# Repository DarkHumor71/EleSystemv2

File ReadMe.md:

# EleSystemv2 - Smart Elevator & Building Management System

A comprehensive IoT-based elevator and building management system that integrates hardware control, electricity expense tracking, and a web-based admin dashboard. The system combines ESP32 microcontrollers for elevator control and QR code authentication with a full-stack web application for building and apartment management.

## 🏗️ Project Overview

EleSystemv2 is a multi-component system designed to modernize building management by:

- **Automated Elevator Control**: ESP32-based elevator controller with floor selection and queue management
- **QR Code Authentication**: Camera module for secure apartment access verification
- **Electricity Monitoring**: Track and calculate power consumption per apartment
- **Web Dashboard**: Modern React admin interface for managing buildings, apartments, and expenses
- **Role-Based Access**: Support for admin, moderator, and resident user roles

## 📁 Project Structure

```
EleSystemv2/
├── backend/              # Node.js/Express REST API
│   ├── config/          # Database and configuration files
│   ├── middleware/      # Authentication and authorization middleware
│   ├── models/          # MongoDB/Mongoose data models
│   └── routes/          # API route handlers
├── client/              # React admin dashboard
│   ├── public/          # Static assets
│   └── src/
│       ├── actions/     # Redux actions
│       ├── components/  # Reusable React components
│       ├── scenes/      # Page-level components
│       ├── reducers/    # Redux reducers
│       └── utils/       # Helper utilities
├── board/               # ESP32 elevator controller firmware
├── camera/              # ESP32-CAM QR code reader firmware
└── CAD/                 # KiCad PCB design files
```

## 🚀 Features

### Backend (REST API)

- **Authentication & Authorization**: JWT-based auth with role-based access control
- **Building Management**: CRUD operations for buildings with soft-delete support
- **Apartment Management**: Manage apartments within buildings, assign moderators
- **Expense Tracking**: Record and retrieve electricity usage data per apartment
- **Session Management**: Secure session handling for active users

### Frontend (React Dashboard)

- **Modern UI**: Material-UI components with light/dark mode
- **Data Visualization**: Charts and graphs for expense tracking
- **Building Administration**: Create and manage multiple buildings
- **Apartment Management**: Register apartments, generate QR codes
- **Expense Reports**: View and analyze electricity consumption
- **User Profiles**: Manage user information and roles

### Hardware Components

- **Elevator Controller** (`board/`):

  - 4-floor elevator control system
  - Button inputs and IR sensors per floor
  - Motor control (up/down)
  - 7-segment display for floor indication
  - Power monitoring and expense calculation
  - WiFi connectivity for data transmission

- **QR Code Reader** (`camera/`):
  - ESP32-CAM based authentication
  - Real-time QR code scanning
  - Server validation for apartment access
  - Scan cooldown to prevent duplicates

## 🛠️ Technology Stack

### Backend

- **Runtime**: Node.js
- **Framework**: Express.js
- **Database**: MongoDB with Mongoose ODM
- **Authentication**: JWT (jsonwebtoken)
- **Validation**: express-validator
- **Password Hashing**: bcryptjs

### Frontend

- **Framework**: React 18.3.1
- **State Management**: Redux Toolkit
- **UI Library**: Material-UI (MUI)
- **Routing**: React Router v7
- **Data Grid**: MUI X Data Grid
- **Charts**: Nivo, Chart.js
- **Form Handling**: Formik

### Hardware

- **Microcontroller**: ESP32 / ESP32-CAM
- **Connectivity**: WiFi (HTTP/HTTPS)
- **Development**: Arduino IDE
- **Libraries**: ESP32QRCodeReader, ArduinoJson, HTTPClient

### PCB Design

- **Tool**: KiCad
- **Modules**: Brain, Cabin, Display, Motor, Sensors

## 📋 Prerequisites

- **Node.js** v14+ and npm
- **MongoDB** v4+ (local or cloud instance)
- **Arduino IDE** with ESP32 board support
- **Git** for version control

## ⚙️ Installation & Setup

### 1. Clone the Repository

```bash
git clone https://github.com/DarkHumor71/EleSystemv2.git
cd EleSystemv2
```

### 2. Backend Setup

```bash
cd backend
npm install
```

Create a `config/default.json` file:

```json
{
  "mongoURI": "mongodb://localhost:27017/elesystem",
  "jwtSecret": "your_jwt_secret_key_here"
}
```

Or create a `.env` file with:

```
MONGO_URI=mongodb://localhost:27017/elesystem
JWT_SECRET=your_jwt_secret_key_here
PORT=5000
```

Start the backend server:

```bash
npm run server    # Development mode with nodemon
npm start         # Production mode
```

### 3. Frontend Setup

```bash
cd client
npm install
```

Update the proxy in `client/package.json` to match your backend URL:

```json
"proxy": "http://localhost:5000/"
```

Start the React development server:

```bash
npm start
```

### 4. Full Stack Development

From the `backend` directory:

```bash
npm run dev    # Runs both backend and frontend concurrently
```

### 5. Hardware Setup

#### Elevator Controller

1. Open `board/board.ino` in Arduino IDE
2. Update WiFi credentials:
   ```cpp
   const char* ssid = "your_wifi_ssid";
   const char* password = "your_wifi_password";
   ```
3. Update the server URL to match your backend IP
4. Upload to ESP32 board

#### Camera Module

1. Open `camera/camera.ino` in Arduino IDE
2. Update WiFi credentials and validation server URL
3. Upload to ESP32-CAM board

## 🔌 API Endpoints

### Authentication

- `POST /api/auth/login` - User login
- `POST /api/auth/apartment` - Apartment authentication

### Buildings

- `GET /api/building/:id` - Get building details
- `POST /api/building` - Create new building
- `PUT /api/building/:id` - Update building
- `DELETE /api/building/:id` - Soft delete building

### Apartments

- `GET /api/apartment/:id` - Get apartment details
- `POST /api/apartment` - Create new apartment
- `PUT /api/apartment/:id` - Update apartment
- `GET /api/apartment/exists` - Validate apartment (for QR authentication)

### Expenses

- `POST /api/expense` - Record electricity usage
- `GET /api/expense/apartment/:id` - Get expenses for apartment
- `GET /api/expense/building/:id` - Get all expenses for building
- `DELETE /api/expense/:id` - Delete expense record

## 🔐 Authentication & Authorization

The system uses JWT tokens with three permission levels:

1. **Admin**: Full system access, manage all buildings and apartments
2. **Moderator**: Building-specific access, manage apartments in their building
3. **Resident**: View personal apartment information and expenses

Middleware components:

- `auth.js` - Validates JWT token
- `admin.js` - Requires admin permissions
- `moderator.js` - Requires moderator permissions
- `building.js` - Validates building-level access
- `sameBuildingMod.js` - Ensures moderator belongs to the target building

## 📊 Data Models

### Building

- Name, email, address, city, state
- Soft delete support
- One-to-many relationship with apartments

### Apartment

- 4-digit PIN for authentication
- Apartment number (unique within building)
- Resident information (first name, last name, email)
- Moderator designation flag
- Reference to parent building

### Expense

- Time duration (in seconds)
- Power consumption (kWh)
- Cost calculation
- Timestamp of recording
- Reference to apartment

### Session

- Active user sessions
- Token management
- Automatic cleanup on server restart

## 🖥️ Dashboard Features

- **Admin Dashboard**: Overview of all buildings, apartments, and expenses
- **Moderator Dashboard**: Building-specific management
- **Apartment Dashboard**: Resident view of their expenses
- **Building List**: Browse and manage buildings
- **Apartment Management**: Add, edit, view apartments
- **Expense Tracking**: Visualize electricity usage over time
- **QR Code Generation**: Create QR codes for apartment authentication
- **Profile Management**: Update user information

## 🔧 Hardware Configuration

### Elevator Controller Pins

- **Buttons**: GPIO 19, 21, 22, 23 (floors 0-3)
- **IR Sensors**: GPIO 18, 5, 17, 16 (floors 0-3)
- **Motor Up**: GPIO 13
- **Motor Down**: GPIO 12
- **7-Segment Display**: Latch (26), Clock (25), Data (27)
- **Power Monitoring**: GPIO 34 (analog sensor)

### Camera Module

- ESP32-CAM with CAMERA_MODEL_AI_THINKER
- QR code scanning with 5-second cooldown
- HTTP validation with backend server

### FreeRTOS controller firmware

`board/board.ino` targets the ESP32 Arduino core, which includes FreeRTOS.
The elevator task runs every 10 ms at priority 4 and owns the buttons, floor
sensors, display, motor outputs, and emergency stop. A priority 1 network task
handles Wi-Fi, session verification, and expense uploads. An event group gates
motor operation on a verified session; a one-item FreeRTOS queue transfers an
expense report after the stop input is pressed. Upload failures are retried
without blocking motor shutdown. A full report queue latches a fault and
prevents another run.

The revised schematic uses an INA228 current monitor on I²C (SDA GPIO 16,
SCL GPIO 17). A third FreeRTOS task reads it and sends current samples through
a one-item queue; the motor task stays responsive if I²C is slow. Install the
`Adafruit INA228` Arduino library and its dependencies before building.
Set `SHUNT_RESISTANCE_OHMS` and `MAX_CURRENT_A` in `board/board.ino` to
match the assembled shunt and motor. The current values are provisional, so
expense measurements need calibration on hardware. The controller will not
enable its ready output until the INA228 initializes. The camera sketch
already uses a FreeRTOS QR scanning task.

## 🎨 Frontend Theming

The dashboard supports light and dark modes with customizable Material-UI themes. Theme configuration is in `client/src/theme.js`.

## 🧪 Testing

```bash
# Backend tests
cd backend
npm test

# Frontend tests
cd client
npm test
```

## 📦 Building for Production

### Frontend

```bash
cd client
npm run build
```

This creates an optimized production build in the `client/build` directory.

### Backend

The backend runs in production mode with:

```bash
cd backend
npm start
```

## 🤝 Contributing

Contributions are welcome! Please follow these steps:

1. Fork the repository
2. Create a feature branch (`git checkout -b feature/AmazingFeature`)
3. Commit your changes (`git commit -m 'Add some AmazingFeature'`)
4. Push to the branch (`git push origin feature/AmazingFeature`)
5. Open a Pull Request

## 📝 License

This project is licensed under the MIT License - see the [LICENSE](LICENSE) file for details.

## 👤 Author

**Mohammad Youssef** (DarkHumor71) **Ahmad Ayoub** (AhmadAybb) 

## 📞 Support

For questions, issues, or feature requests, please open an issue on the GitHub repository.

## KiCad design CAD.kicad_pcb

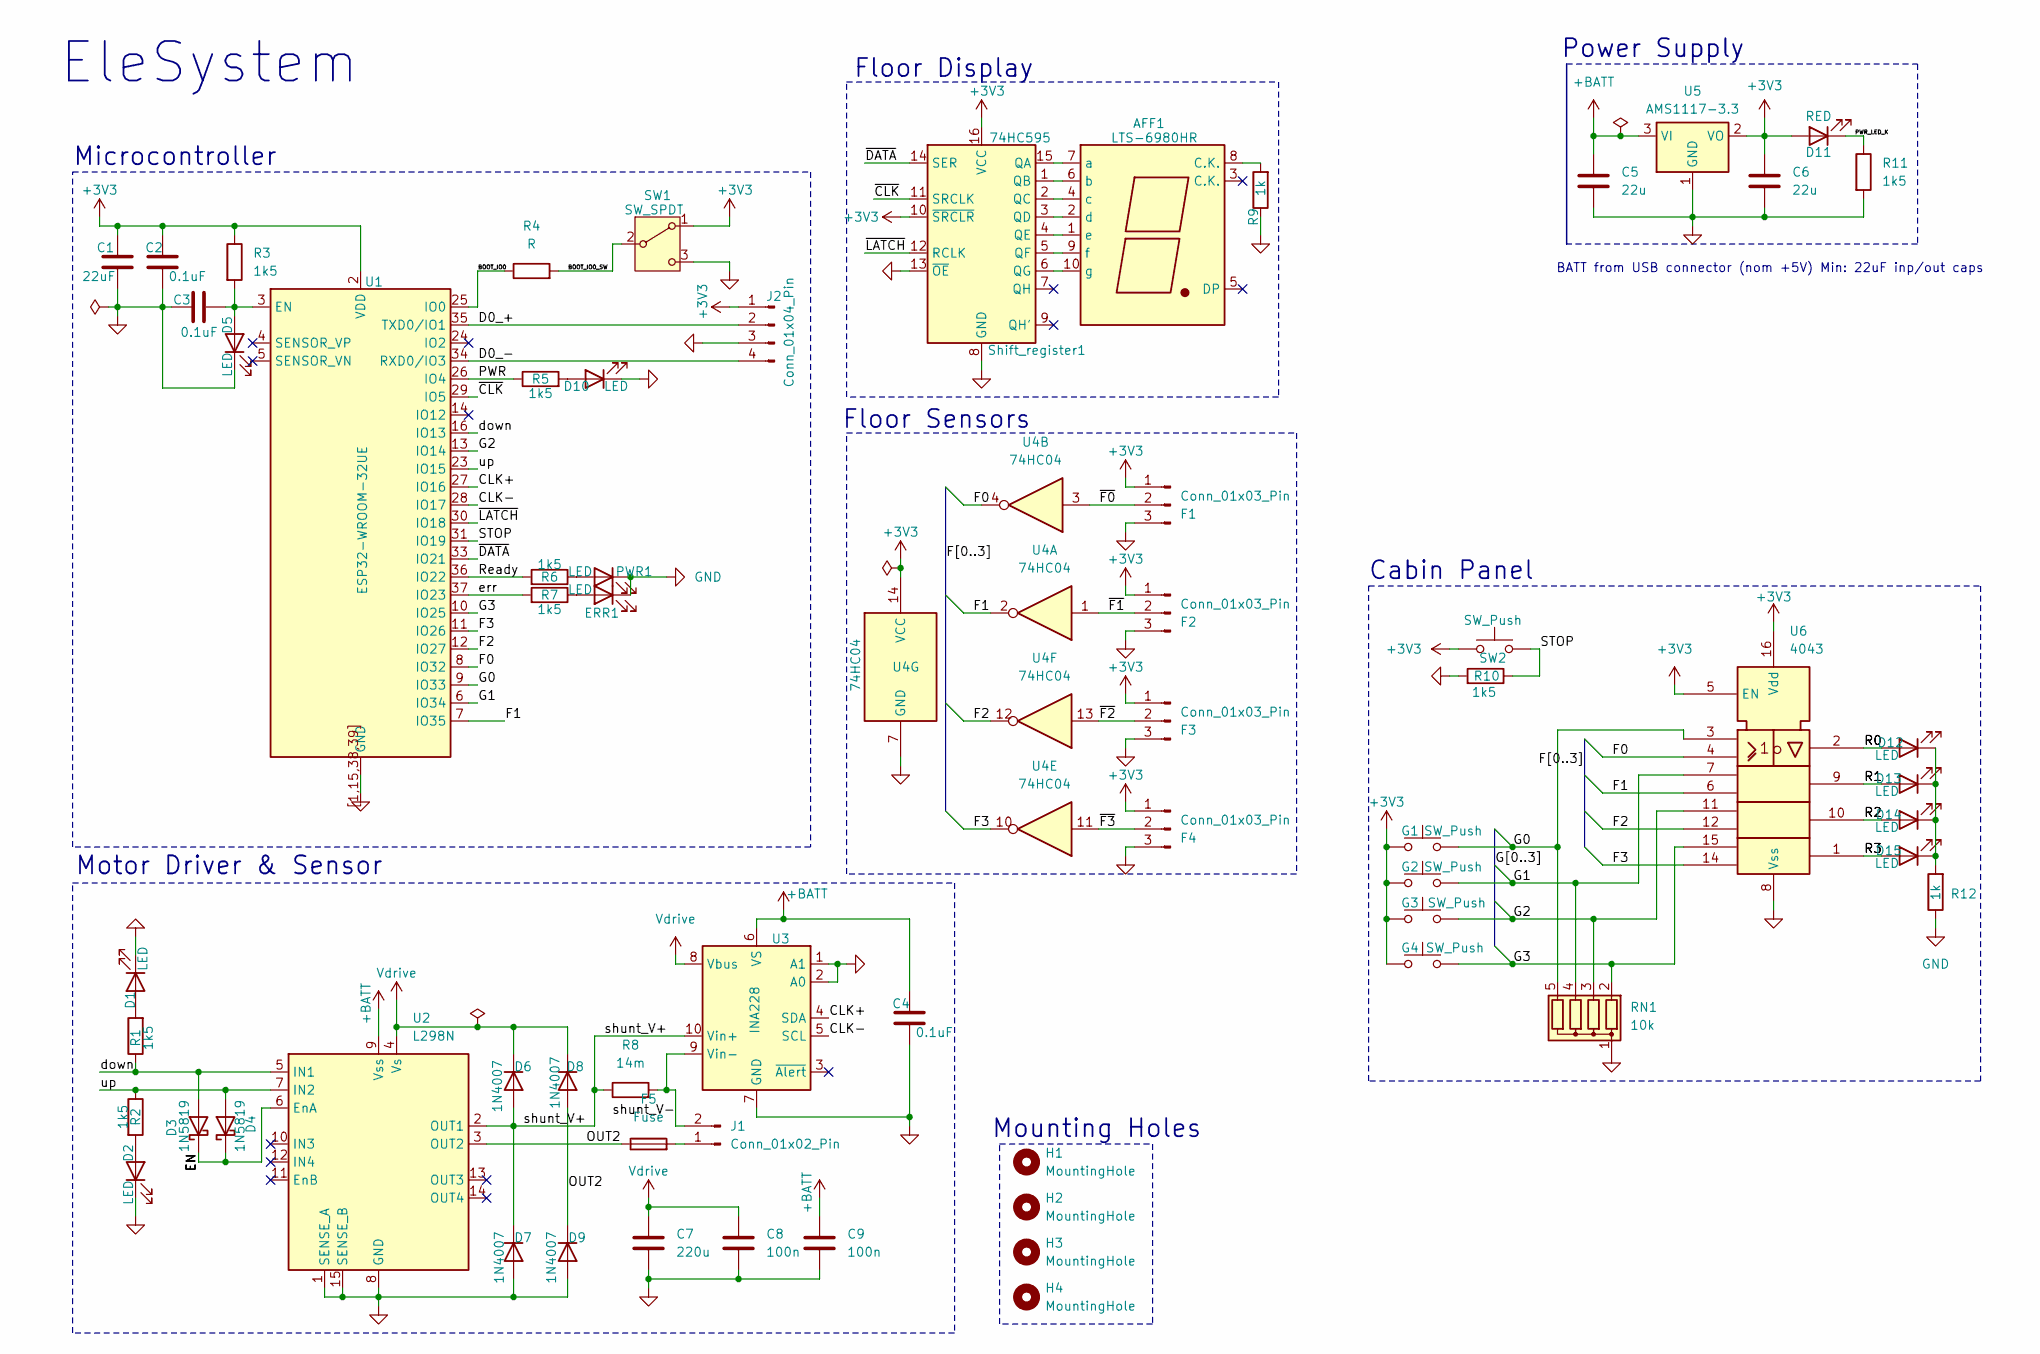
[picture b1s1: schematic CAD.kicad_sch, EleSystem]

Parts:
AFF1: LTS-6980HR; 7SegmentLED_LTS6760_LTS6780
C1: 22uF; C_0805_2012Metric
C2, C3, C4: 0.1uF; C_0402_1005Metric
C5, C6: 22u; C_0805_2012Metric
C7: 220u; C_Elec_8x10.2
C8, C9: 100n; C_0805_2012Metric
D1, D2, D5, D10: LED; LED_0603_1608Metric
D3, D4: 1N5819; D_1206_3216Metric
D6, D7, D8, D9: 1N4007; D_1206_3216Metric
D11: RED; LED_0603_1608Metric
D12, D13, D14, D15: LED; LED_1812_4532Metric_Pad1.30x3.40mm_HandSolder
ERR1: LED; LED_0603_1608Metric
F1, F2, F3, F4: Conn_01x03_Pin; PinHeader_1x03_P1.00mm_Vertical_SMD_Pin1Right
F5: Fuse; Fuse_0603_1608Metric
G1, G2, G3, G4: SW_Push; SW_PUSH_6mm_H7.3mm
H1, H2, H3, H4: MountingHole; MountingHole_2.2mm_M2
J1: Conn_01x02_Pin; PinHeader_1x02_P2.54mm_Vertical_SMD_Pin1Left
J2: Conn_01x04_Pin; PinHeader_1x04_P1.27mm_Vertical_SMD_Pin1Right
PWR1: LED; LED_0603_1608Metric
R1, R2, R3, R5, R6, R7, R10, R11: 1k5; R_0603_1608Metric
R4: R; R_0603_1608Metric
R8: 14m; R_2512_6332Metric
R9, R12: 1k; R_0603_1608Metric
RN1: 10k; R_Array_SIP5
SW1: SW_SPDT; SW_Slide_SPDT_Straight_CK_OS102011MS2Q
SW2: SW_Push; SW_Push_1P1T_NO_CK_KSC9xxG
Shift_register1: 74HC595; JEITA_SOIC-16_3.9x9.9mm_P1.27mm
U1: ESP32-WROOM-32UE
U2: L298N; TO-220-15_P2.54x5.08mm_StaggerOdd_Lead4.58mm_Vertical
U3: INA228; SMDIP-10_W7.62mm
U4: 74HC04; SSOP-16_4.4x5.2mm_P0.65mm
U5: AMS1117-3.3; SOT-223-3_TabPin2
U6: 4043; DIP-16_W7.62mm

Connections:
+3V3: C1.1, C2.1, C6.1, D11.2 (A), F1.1, F2.1, F3.1, F4.1, G1.1, G2.1, G3.1, G4.1, J2.1, R3.1, SW1.1 (A), SW2.2, Shift_register1.10 (~SRCLR), Shift_register1.16 (VCC), U1.2 (VDD), U4.14 (VCC), U5.2 (VO), U6.5 (EN), U6.16 (Vdd)
+BATT: C4.1, C5.1, C9.1, U2.9 (Vss), U3.6 (VS), U5.3 (VI); also elsewhere on the board
/BOOT_IO0: R4.1, U1.25 (IO0)
/BOOT_IO0_SW: R4.2, SW1.2 (B)
/CLK+: U1.27 (IO16), U3.4 (SDA)
/CLK-: U1.28 (IO17), U3.5 (SCL)
/D0_+: J2.2, U1.35 (TXD0/IO1)
/D0_-: J2.4, U1.34 (RXD0/IO3)
/EN: D3.1 (K), D4.1 (K), U2.6 (EnA)
/F0: U1.8 (IO32), U4.4, U6.4
/F1: U1.7 (IO35), U4.2, U6.6
/F2: U1.12 (IO27), U4.12, U6.12
/F3: U1.11 (IO26), U4.10, U6.14
/G0: G1.2, RN1.5 (R4), U1.9 (IO33), U6.3
/G1: G2.2, RN1.4 (R3), U1.6 (IO34), U6.7
/G2: G3.2, RN1.3 (R2), U1.13 (IO14), U6.11
/G3: G4.2, RN1.2 (R1), U1.10 (IO25), U6.15
/OUT2: D8.2 (A), D9.1 (K), F5.1, U2.3 (OUT2)
/PWR: R5.1, U1.26 (IO4)
/PWR_LED_K: D11.1 (K), R11.1
/R0: D12.2 (A), U6.2
/R1: D13.2 (A), U6.9
/R2: D14.2 (A), U6.10
/R3: D15.2 (A), U6.1
/Ready: R6.2, U1.36 (IO22)
/STOP: R10.1, SW2.1, U1.31 (IO19)
/down: D3.2 (A), R1.1, U1.16 (IO13), U2.5 (IN1)
/err: R7.2, U1.37 (IO23)
/shunt_V+: D6.2 (A), D7.1 (K), R8.1, U2.2 (OUT1), U3.10 (Vin+)
/shunt_V-: J1.2, R8.2, U3.9 (Vin-)
/up: D4.2 (A), R2.1, U1.23 (IO15), U2.7 (IN2)
/~CLK: Shift_register1.11 (SRCLK), U1.29 (IO5)
/~DATA: Shift_register1.14 (SER), U1.33 (IO21)
/~F0: F1.2, U4.3
/~F1: F2.2, U4.1
/~F2: F3.2, U4.13
/~F3: F4.2, U4.11
/~LATCH: Shift_register1.12 (RCLK), U1.30 (IO18)
GND: C1.2, C2.2, C3.1, C4.2, C5.2, C6.2, C7.2, C8.2, C9.2, D1.1 (K), D2.1 (K), D5.1 (K), D7.2 (A), D9.2 (A), D10.1 (K), ERR1.1 (K), F1.3, F2.3, F3.3, F4.3, J2.3, PWR1.1 (K), R9.1, R10.2, R11.2, R12.1, RN1.1 (common), SW1.3 (C), Shift_register1.8 (GND), Shift_register1.13 (~OE), U1.1 (GND), U1.15 (GND), U1.38 (GND), U1.39 (GND), U1.[1,15,38,39] (GND), U2.1 (SENSE_A), U2.8 (GND), U2.15 (SENSE_B), U3.1 (A1), U3.2 (A0), U3.7 (GND), U4.7 (GND), U5.1 (GND), U6.8 (Vss); also elsewhere on the board
unnamed: AFF1.8 (C.K.), R9.2
unnamed: AFF1.7 (a), Shift_register1.15 (QA)
unnamed: AFF1.6 (b), Shift_register1.1 (QB)
unnamed: AFF1.4 (c), Shift_register1.2 (QC)
unnamed: AFF1.2 (d), Shift_register1.3 (QD)
unnamed: AFF1.1 (e), Shift_register1.4 (QE)
unnamed: AFF1.9 (f), Shift_register1.5 (QF)
unnamed: AFF1.10 (g), Shift_register1.6 (QG)
unnamed: D1.2 (A), R1.2
unnamed: D2.2 (A), R2.2
unnamed: C3.2, D5.2 (A), R3.2, U1.3 (EN)
unnamed: D10.2 (A), R5.2
unnamed: D12.1 (K), D13.1 (K), D14.1 (K), D15.1 (K), R12.2
unnamed: ERR1.2 (A), R7.1
unnamed: F5.2, J1.1
unnamed: PWR1.2 (A), R6.1
Vdrive: C7.1, C8.1, D6.1 (K), D8.1 (K), U2.4 (Vs), U3.8 (Vbus)

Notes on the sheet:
Cabin Panel
Floor Display
Motor Driver & Sensor
BATT from USB connector (nom +5V) Min: 22uF inp/out caps
EleSystem
Microcontroller
Mounting Holes
Floor Sensors
Power Supply

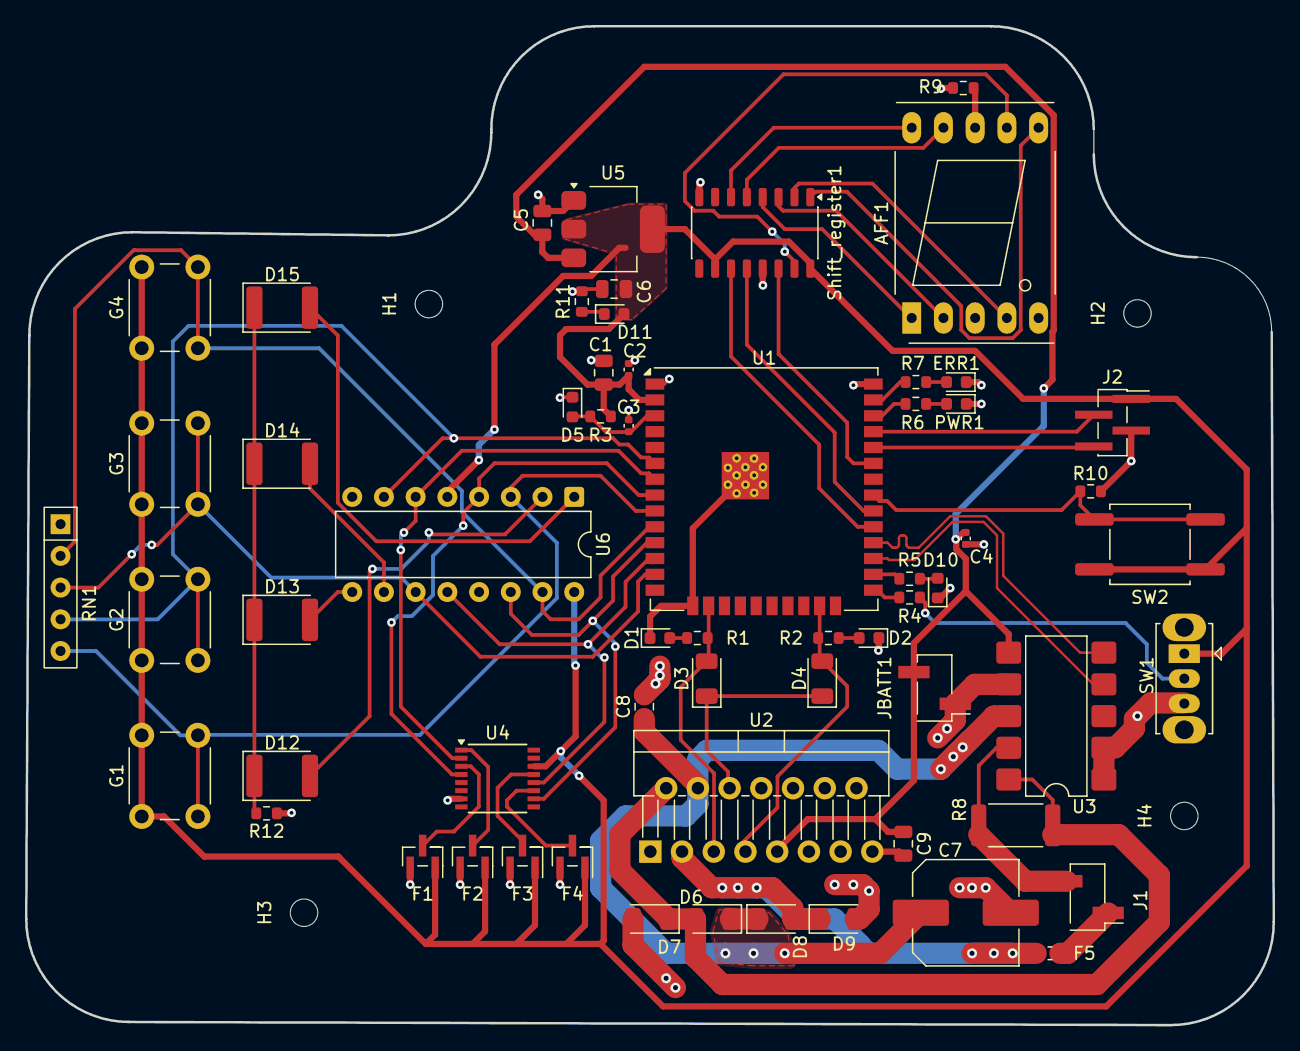
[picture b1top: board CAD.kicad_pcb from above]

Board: 2 copper layers, 99.9 x 80.0 mm, 65 parts (0 on the bottom side), 56 nets.

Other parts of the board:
JBATT1: Conn_01x02_Pin; PinHeader_1x02_P2.54mm_Vertical_SMD_Pin1Left

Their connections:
+BATT: JBATT1.2; also elsewhere on the board
GND: JBATT1.1; also elsewhere on the board

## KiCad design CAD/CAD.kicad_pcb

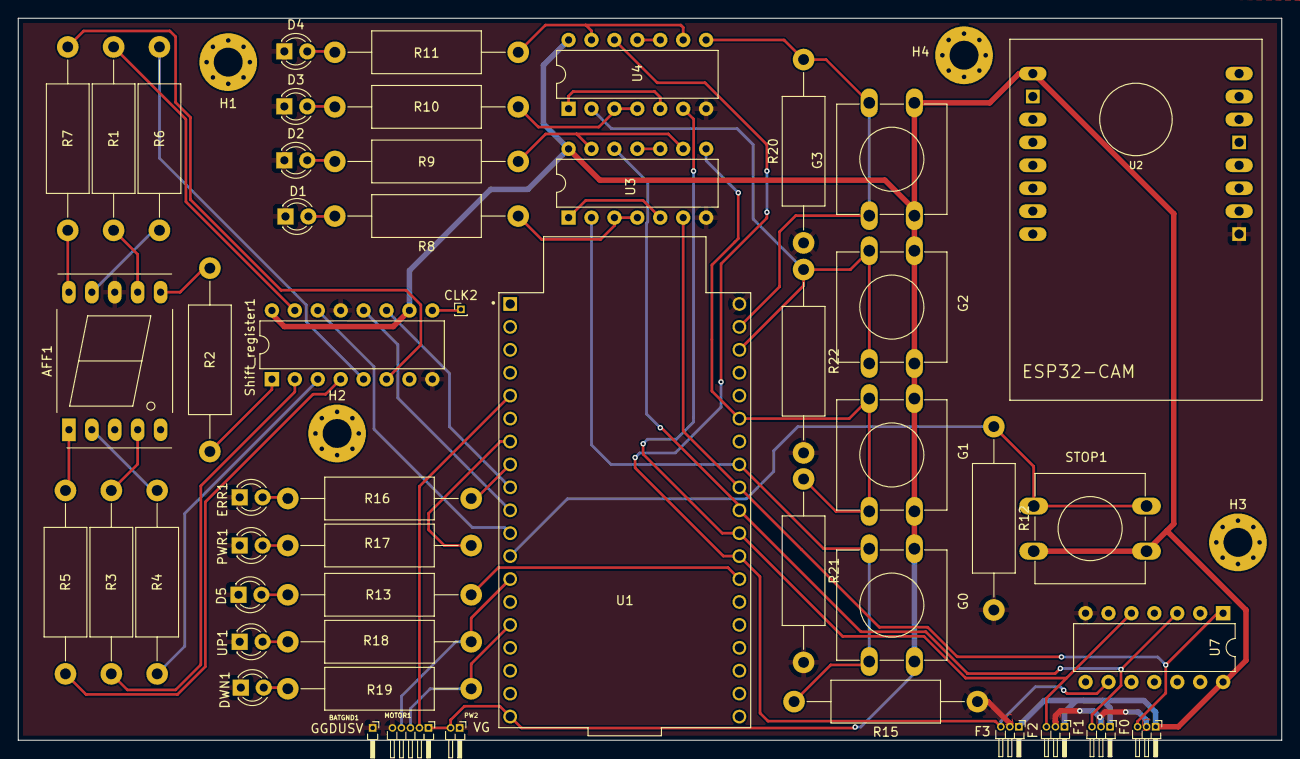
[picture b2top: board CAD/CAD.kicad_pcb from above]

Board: 2 copper layers, 140.0 x 80.0 mm, 54 parts (0 on the bottom side), 52 nets.

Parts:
AFF1: LTS-6980HR; 7SegmentLED_LTS6760_LTS6780
BATGND1: Conn_01x01_Socket; PinHeader_1x01_P1.00mm_Horizontal
CLK2: Conn_01x01_Pin; PinHeader_1x01_P1.00mm_Vertical
D1, D2, D3, D4, D5: LED; LED_D3.0mm
DWN1: LED; LED_D3.0mm
ERR1: LED; LED_D3.0mm
F0, F1, F2, F3: Conn_01x03_Pin; PinHeader_1x03_P1.00mm_Horizontal
G0, G1, G2, G3: SW_Push; SW_PUSH-12mm
H1, H2, H3, H4: MountingHole_Pad; MountingHole_3.2mm_M3_Pad_Via
MOTOR1: Conn_01x05_Pin; PinHeader_1x05_P1.00mm_Horizontal
PW2: Conn_01x02_Pin; PinHeader_1x02_P1.00mm_Horizontal
PWR1: LED; LED_D3.0mm
R1, R2, R3, R4, R5, R6, R7, R16, R17, R18, R19: 100; R_Axial_DIN0414_L11.9mm_D4.5mm_P20.32mm_Horizontal
R8, R9, R10, R11, R12, R13, R15, R20, R21, R22: R; R_Axial_DIN0414_L11.9mm_D4.5mm_P20.32mm_Horizontal
STOP1: SW_Push; SW_PUSH-12mm
Shift_register1: 74HC595; DIP-16_W7.62mm
U1: ESP32-DEVKITC; MODULE_ESP32-DEVKITC
U2: ESP32-CAM
U3, U4: 74HC02; DIP-14_W7.62mm
U7: 74HC04; DIP-14_W7.62mm
UP1: LED; LED_D3.0mm

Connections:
/Brain/Vsens: MOTOR1.2, U1.5 (IO34)
/Brain/down: MOTOR1.4, R18.1, U1.13 (IO12)
/Brain/err: R16.2, U1.8 (IO33)
/Brain/up: MOTOR1.3, R19.1, U1.15 (IO13)
/Brain/~CLK: Shift_register1.11 (SRCLK), U1.9 (IO25)
/Brain/~DATA: Shift_register1.14 (SER), U1.11 (IO27)
/Brain/~LATCH: Shift_register1.12 (RCLK), U1.10 (IO26)
/Cabin/F0: F0.3, U1.30 (IO18), U3.6, U7.1
/Cabin/F1: F1.3, U1.29 (IO5), U3.12, U7.3
/Cabin/F2: F2.3, U1.28 (IO17), U4.6, U7.5
/Cabin/F3: F3.3, U1.27 (IO16), U4.12, U7.9
/Cabin/G0: G0.2, R15.2, U1.31 (IO19), U3.2
/Cabin/G1: G1.2, R21.1, U1.33 (IO21), U3.8
/Cabin/G2: G2.2, R22.1, U1.36 (IO22), U4.2
/Cabin/G3: G3.2, R20.2, U1.37 (IO23), U4.8
GND: AFF1.8 (C.K.), BATGND1.1, D1.1 (K), D2.1 (K), D3.1 (K), D4.1 (K), D5.1 (K), DWN1.1 (K), ERR1.1 (K), F0.2, F1.2, F2.2, F3.2, MOTOR1.5, PW2.1, PWR1.1 (K), R12.2, R15.1, R20.1, R21.2, R22.2, Shift_register1.8 (GND), Shift_register1.13 (~OE), U1.38 (GND3), U2.P$1 (GND@1), U3.7 (GND), U4.7 (GND), U7.7 (GND), UP1.1 (K)
unnamed: AFF1.7 (a), R1.2
unnamed: AFF1.6 (b), R2.2
unnamed: AFF1.4 (c), R3.2
unnamed: AFF1.2 (d), R4.2
unnamed: AFF1.1 (e), R5.2
unnamed: AFF1.9 (f), R6.2
unnamed: AFF1.10 (g), R7.2
unnamed: CLK2.1, Shift_register1.9 (QH')
unnamed: D1.2 (A), R8.2
unnamed: D2.2 (A), R9.2
unnamed: D3.2 (A), R10.2
unnamed: D4.2 (A), R11.2
unnamed: D5.2 (A), R13.2
unnamed: DWN1.2 (A), R19.2
unnamed: ERR1.2 (A), R16.1
unnamed: PWR1.2 (A), R17.1
unnamed: R8.1, U3.3, U3.4
unnamed: R9.1, U3.9, U3.13
unnamed: R10.1, U4.3, U4.4
unnamed: R11.1, U4.9, U4.13
unnamed: R1.1, Shift_register1.15 (QA)
unnamed: R2.1, Shift_register1.1 (QB)
unnamed: R3.1, Shift_register1.2 (QC)
unnamed: R4.1, Shift_register1.3 (QD)
unnamed: R5.1, Shift_register1.4 (QE)
unnamed: R6.1, Shift_register1.5 (QF)
unnamed: R7.1, Shift_register1.6 (QG)
unnamed: R13.1, U1.26 (IO4)
unnamed: R12.1, STOP1.1, U1.12 (IO14)
unnamed: R17.2, U1.7 (IO32)
unnamed: U3.1, U3.5
unnamed: U3.10, U3.11
unnamed: U4.1, U4.5
unnamed: U4.10, U4.11
unnamed: R18.2, UP1.2 (A)
VCC: F0.1, F1.1, F2.1, F3.1, G0.1, G1.1, G2.1, G3.1, MOTOR1.1, PW2.2, STOP1.2, Shift_register1.10 (~SRCLR), Shift_register1.16 (VCC), U1.19 (EXT_5V), U2.P$9 (5V), U3.14 (VCC), U4.14 (VCC), U7.14 (VCC)

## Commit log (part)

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2025-02-19 new file: .gitignore new file: API/auth.js new file: API/post.js new file: API/profile.js new file: API/users.js new file: client/.gitignore new file: client/README.md new file: client/package-lock.j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
2025-02-19 new file: models/Apartment.js new file: models/Building.js new file: models/Expense.js deleted: models/Post.js deleted: models/Profile.js modified: models/User.js new file: routes/API/apartment.js mo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
2025-02-19 modified: config/default.json modified: middleware/brain.js modified: middleware/moderator.js modified: middleware/owner.js modified: models/Apartment.js modified: models/Building.js modified: models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
2025-02-20 modified: client/.gitignore modified: client/README.md modified: client/package-lock.json modified: client/package.json new file: client/public/assets/user.png deleted: client/public/error/error-404-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
2025-02-20 modified: client/src/index.js modified: client/src/reducers/alert.js
2025-02-20 deleted: theme/401.html deleted: theme/404.html deleted: theme/500.html deleted: theme/assets/demo/chart-area-demo.js deleted: theme/assets/demo/chart-bar-demo.js deleted: theme/assets/demo/chart-pie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
2025-02-20 new file: LISENCE new file: ReadMe.md
2025-02-20 Create LICENSE
2025-02-22 new file: middleware/admin.js modified: middleware/auth.js deleted: middleware/brain.js new file: middleware/building.js modified: middleware/moderator.js deleted: middleware/owner.js modified: model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
2025-02-25 modified: middleware/admin.js modified: middleware/auth.js modified: models/Apartment.js modified: routes/API/apartment.js modified: routes/API/auth.js
2025-02-27 modified: client/package-lock.json
2025-02-27 modified: models/Expense.js modified: models/User.js modified: routes/API/apartment.js modified: routes/API/auth.js modified: routes/API/expense.js modified: routes/API/users.js
2025-03-01 modified: client/package-lock.json modified: client/package.json modified: client/src/App.js modified: client/src/actions/auth.js modified: client/src/actions/types.js modified: client/src/index.css 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
2025-03-03 modified: client/package-lock.json renamed: client/src/App.js -> client/src/App.jsx new file: client/src/Layout/Alert.jsx modified: client/src/actions/auth.js modified: client/src/actions/types.js de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
2025-03-05 modified: client/src/App.jsx modified: client/src/actions/auth.js new file: client/src/actions/building.js new file: client/src/reducers/building.js modified: client/src/reducers/index.js modified: c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
2025-03-05 modified: client/package.json
2025-03-05 modified: routes/API/expense.js
2025-03-05 modified: client/package-lock.json modified: client/package.json modified: client/src/App.jsx modified: client/src/Layout/Alert.jsx modified: client/src/Layout/MainLayout.jsx modified: client/src/act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
2025-03-05 deleted: client/package-lock.json modified: client/package.json modified: client/src/actions/auth.js modified: client/src/index.css new file: client/src/setupProxy.js modified: server.js
2025-03-05 modified: client/src/setupProxy.js
2025-03-05 modified: .gitignore modified: client/.gitignore new file: client/package-lock.json modified: client/package.json modified: client/src/App.jsx modified: client/src/Layout/MainLayout.jsx modified: cli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
2025-03-05 modified: client/package-lock.json modified: client/src/scenes/global/Sidebar.jsx
2025-03-05 new file: .env modified: .gitignore new file: client/.env
2025-03-08 modified: client/src/App.jsx modified: client/src/scenes/contacts/index.jsx modified: client/src/scenes/dashboard/index.jsx modified: client/src/scenes/dashboard/mod.jsx new file: client/src/scenes/d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
2025-03-09 modified: client/src/App.jsx modified: client/src/components/ProgressCircle.jsx modified: client/src/scenes/contacts/index.jsx modified: client/src/scenes/dashboard/apart.jsx modified: client/src/sce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
2025-03-09 modified: client/src/App.jsx modified: client/src/Layout/MainLayout.jsx modified: client/src/scenes/dashboard/index.jsx modified: client/src/scenes/global/Topbar.jsx new file: client/src/scenes/profi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
2025-03-09 modified: client/src/App.jsx modified: client/src/Layout/MainLayout.jsx modified: client/src/actions/auth.js modified: client/src/scenes/global/Sidebar.jsx modified: client/src/scenes/login/login.jsx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
2025-03-09 modified: client/src/Layout/MainLayout.jsx
2025-03-09 modified: client/src/App.jsx
2025-03-09 modified: client/src/App.jsx modified: client/src/Layout/MainLayout.jsx
2025-03-11 modified: client/src/App.jsx modified: client/src/Layout/MainLayout.jsx modified: client/src/scenes/contacts/index.jsx modified: client/src/scenes/dashboard/index.jsx modified: client/src/scenes/glob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
2025-03-11 modified: client/src/App.jsx modified: client/src/actions/auth.js modified: client/src/actions/building.js modified: client/src/actions/types.js modified: client/src/reducers/auth.js modified: client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
2025-03-12 modified: models/Apartment.js deleted: models/User.js deleted: routes/API/users.js
2025-03-12 modified: client/src/App.jsx renamed: client/src/scenes/contacts/index.jsx -> client/src/scenes/building/building.jsx modified: client/src/scenes/dashboard/admin.jsx
2025-03-12 modified: client/src/App.jsx modified: client/src/Layout/MainLayout.jsx modified: client/src/actions/auth.js modified: client/src/actions/types.js new file: client/src/components/routing/privateroute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
2025-03-12 modified: client/src/App.jsx new file: client/src/scenes/apartment/apartments.jsx renamed: client/src/scenes/contacts/index.jsx -> client/src/scenes/buildings/list_of_building.jsx modified: client/sr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
2025-03-12 modified: client/src/scenes/apartment/apartments.jsx modified: client/src/scenes/expensess/index.jsx modified: middleware/moderator.js modified: models/Apartment.js modified: routes/API/apartment.js 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
2025-03-13 modified: client/src/actions/auth.js modified: client/src/scenes/login/login.jsx modified: routes/API/auth.js
2025-03-14 renamed: .env -> backend/.env renamed: .gitignore -> backend/.gitignore renamed: config/db.js -> backend/config/db.js renamed: config/default.json -> backend/config/default.json renamed: middleware/a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
2025-03-14 modified: client/src/App.jsx modified: client/src/scenes/dashboard/mod.jsx new file: client/src/scenes/expensess/apr_expenses.jsx renamed: client/src/scenes/expensess/index.jsx -> client/src/scenes/e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
2025-03-14 deleted: backend/package-lock.json modified: backend/package.json new file: package.json
2025-03-14 deleted: package.json
2025-03-14 modified: backend/routes/API/expense.js modified: client/src/App.jsx modified: client/src/scenes/dashboard/mod.jsx modified: client/src/scenes/expensess/apr_expenses.jsx modified: client/src/scenes/e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
2025-03-14 modified: client/src/App.jsx modified: client/src/scenes/dashboard/mod.jsx new file: client/src/scenes/login/v.jsx
2025-03-14 modified: backend/routes/API/auth.js modified: client/src/actions/auth.js modified: client/src/actions/types.js modified: client/src/reducers/auth.js deleted: client/src/reducers/building.js modified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
2025-03-14 modified: backend/routes/API/apartment.js modified: client/src/App.jsx modified: client/src/scenes/apartment/apartments.jsx
2025-03-16 modified: client/.env modified: client/src/App.jsx modified: client/src/scenes/expensess/apr_expenses.jsx modified: client/src/scenes/expensess/building_expenses.jsx
2025-03-16 modified: backend/routes/API/auth.js
2025-03-16 modified: backend/models/Apartment.js modified: client/src/App.jsx new file: client/src/actions/apartment.js modified: client/src/actions/auth.js modified: client/src/actions/building.js modified: cl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
2025-03-17 modified: backend/routes/API/apartment.js modified: client/src/App.jsx modified: client/src/actions/apartment.js new file: client/src/actions/expense.js modified: client/src/actions/types.js modified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
2025-04-11 added react base url and disable host check
2025-04-11 added building id to render on sign in of moderator
2025-04-11 modified pin body
2025-04-12 fixes
2025-04-12 refactored
2025-04-12 added softDelete and recover methods to the schema
2025-04-12 refactored cleaned code
2025-04-12 split some permission
2025-04-13 modified: client/src/scenes/dashboard/apart.jsx
2025-04-14 fixed errors
2025-04-14 deleted mock board
2025-04-14 fixed data structure upon auth
2025-04-14 refactor
2025-04-14 fixed redux data structure
2025-04-14 documentation fix
2025-04-14 created expense fetch for apartment
2025-04-14 created linechart for simpler viewing
2025-04-14 added loadapartment function after logging in
2025-04-14 removed
2025-04-14 initializing for tests
2025-04-14 made all fields dynamic+ added qr code that contains the apartment pass
2025-04-14 updated dispatches
2025-04-15 remove download
2025-04-15 remove redundant
2025-04-15 fix graph
2025-04-15 @dev
2025-04-15 added auth to building api
2025-04-15 fixed the bug in the building.js file
2025-04-15 removed sidebar page
2025-04-15 added update path for updating apartment info
2025-04-15 modified register building fixed admin login issue
2025-04-15 modified admin issue and redux structure
2025-04-15 login reclean
2025-04-15 fixed all routing
2025-04-15 performed backend talks
2025-04-15 fixed register logout on fail
2025-04-15 added transactional support to building routes
2025-04-15 added checks for building
2025-04-16 modified: backend/package.json modified: backend/routes/API/building.js modified: client/src/scenes/dashboard/admin.jsx
2025-04-16 modified: client/src/scenes/form/qrcode.jsx
2025-04-17 applyed name change
2025-04-17 made qrcode path protected
2025-04-17 removed charts
2025-04-17 del building
2025-04-17 fix aprts
2025-04-17 fix expenses
2025-04-17 del build
2025-04-17 fix expense
2025-04-17 del apt
2025-04-17 fix routes
2025-04-17 added types
2025-04-17 added qrcode comp
2025-04-17 added optionality
2025-04-17 refc
2025-04-18 documentation: added documentation for the backend
2025-04-22 modified: backend/config/default.json modified: backend/routes/API/apartment.js modified: backend/routes/API/expense.js modified: backend/server.js modified: client/package.json modified: client/src/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
2025-04-22 added session autoload
2025-04-22 created session schema
2025-04-22 added apartment routes to check for session
2025-04-22 added expense route to account for current expense
2025-04-23 added ESP codes
2025-04-23 updated favicon.ico
2025-04-23 fixed error upon null chart
2025-04-23 fixed download button
2025-04-23 fixed admin dash and added autorefresh feature
2025-04-23 fixed mod dash to delete an apartment
2025-05-04 modified to account for multiple sessions
2025-05-14 fixed bugs
2025-05-15 modified: board/board.ino
2025-05-29 final
2025-08-23 translate to ts
2025-08-23 initial struc
2025-08-23 frontend translation
2025-08-31 backend
2025-11-08 updated reaadme
2026-06-20 Remove sensitive data from backend/.env
    Removed sensitive environment variables from .env file.

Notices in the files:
ReadMe.md:
License: MIT
